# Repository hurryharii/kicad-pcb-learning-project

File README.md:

# Motor Driver Circuit PCB — Work in Progress

## Overview
This project is a motor driver circuit PCB designed using KiCad. It is part of my learning journey in electronics and PCB design.

## Components
- 7805 voltage regulator
- 1N4007 diodes
- Capacitors
- Motor connectors
- Test points

## Current Status
The PCB layout is unfinished, with routing and design checks still pending. It has not yet been fabricated or physically tested.

## Screenshots

### PCB Layout

### 3D PCB View

## Next Steps
- Complete the remaining PCB routing
- Run electrical and design rule checks
- Verify component footprints and connections
- Review the design before fabrication

This project documents my ongoing learning in motor driver circuit design and PCB layout using KiCad.

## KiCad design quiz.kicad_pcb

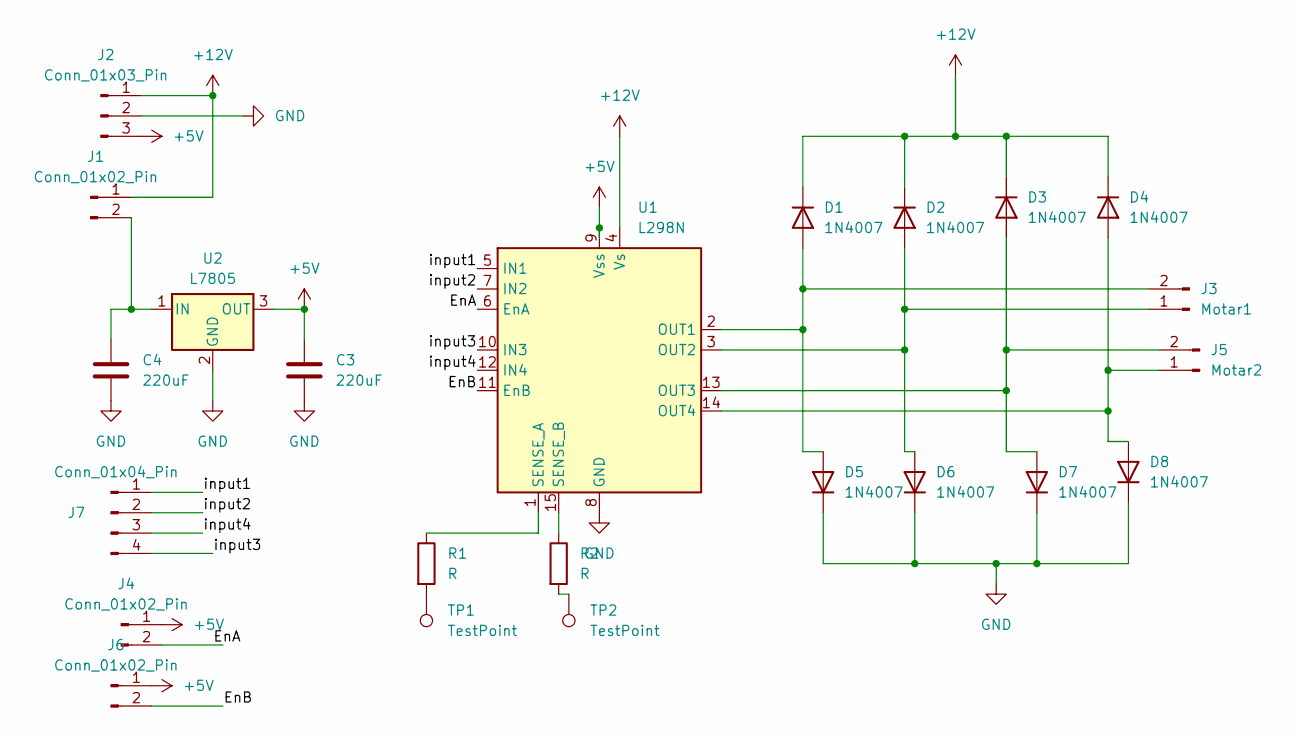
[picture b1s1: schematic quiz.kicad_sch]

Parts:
C3, C4: 220uF; CP_Radial_D10.0mm_P3.50mm
D1, D2, D3, D4, D5, D6, D7, D8: 1N4007; D_DO-41_SOD81_P10.16mm_Horizontal
J1, J4, J6: Conn_01x02_Pin; PinHeader_1x02_P2.54mm_Vertical
J2: Conn_01x03_Pin; TerminalBlock_Phoenix_MPT-0,5-3-2.54_1x03_P2.54mm_Horizontal
J3: Motar1; TerminalBlock_Phoenix_MKDS-1,5-2_1x02_P5.00mm_Horizontal
J5: Motar2; TerminalBlock_Phoenix_MKDS-1,5-2_1x02_P5.00mm_Horizontal
J7: Conn_01x04_Pin; PinHeader_1x04_P2.54mm_Vertical
R1, R2: R; R_0201_0603Metric_Pad0.64x0.40mm_HandSolder
TP1, TP2: TestPoint; TestPoint_Keystone_5010-5014_Multipurpose
U1: L298N; TO-220-15_P2.54x5.08mm_StaggerOdd_Lead4.58mm_Vertical
U2: L7805; TO-220-3_Vertical

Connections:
+5V: C3.1, J2.3, J4.1, J6.1, U1.9 (Vss), U2.3 (OUT)
+12V: D1.1 (K), D2.1 (K), D3.1 (K), D4.1 (K), J1.1, J2.1, U1.4 (Vs)
/EnA: J4.2, U1.6 (EnA)
/EnB: J6.2, U1.11 (EnB)
/input1: J7.1, U1.5 (IN1)
/input2: J7.2, U1.7 (IN2)
/input3: J7.4, U1.10 (IN3)
/input4: J7.3, U1.12 (IN4)
GND: C3.2, C4.2, D5.1 (K), D6.1 (K), D7.1 (K), D8.1 (K), J2.2, U1.8 (GND), U2.2 (GND)
unnamed: D1.2 (A), D5.2 (A), J3.2, U1.2 (OUT1)
unnamed: D2.2 (A), D6.2 (A), J3.1, U1.3 (OUT2)
unnamed: D3.2 (A), D7.2 (A), J5.2, U1.13 (OUT3)
unnamed: D4.2 (A), D8.2 (A), J5.1, U1.14 (OUT4)
unnamed: C4.1, J1.2, U2.1 (IN)
unnamed: R1.2, TP1.1 (1_1)
unnamed: R2.2, TP2.1 (1_1)
unnamed: R1.1, U1.1 (SENSE_A)
unnamed: R2.1, U1.15 (SENSE_B)

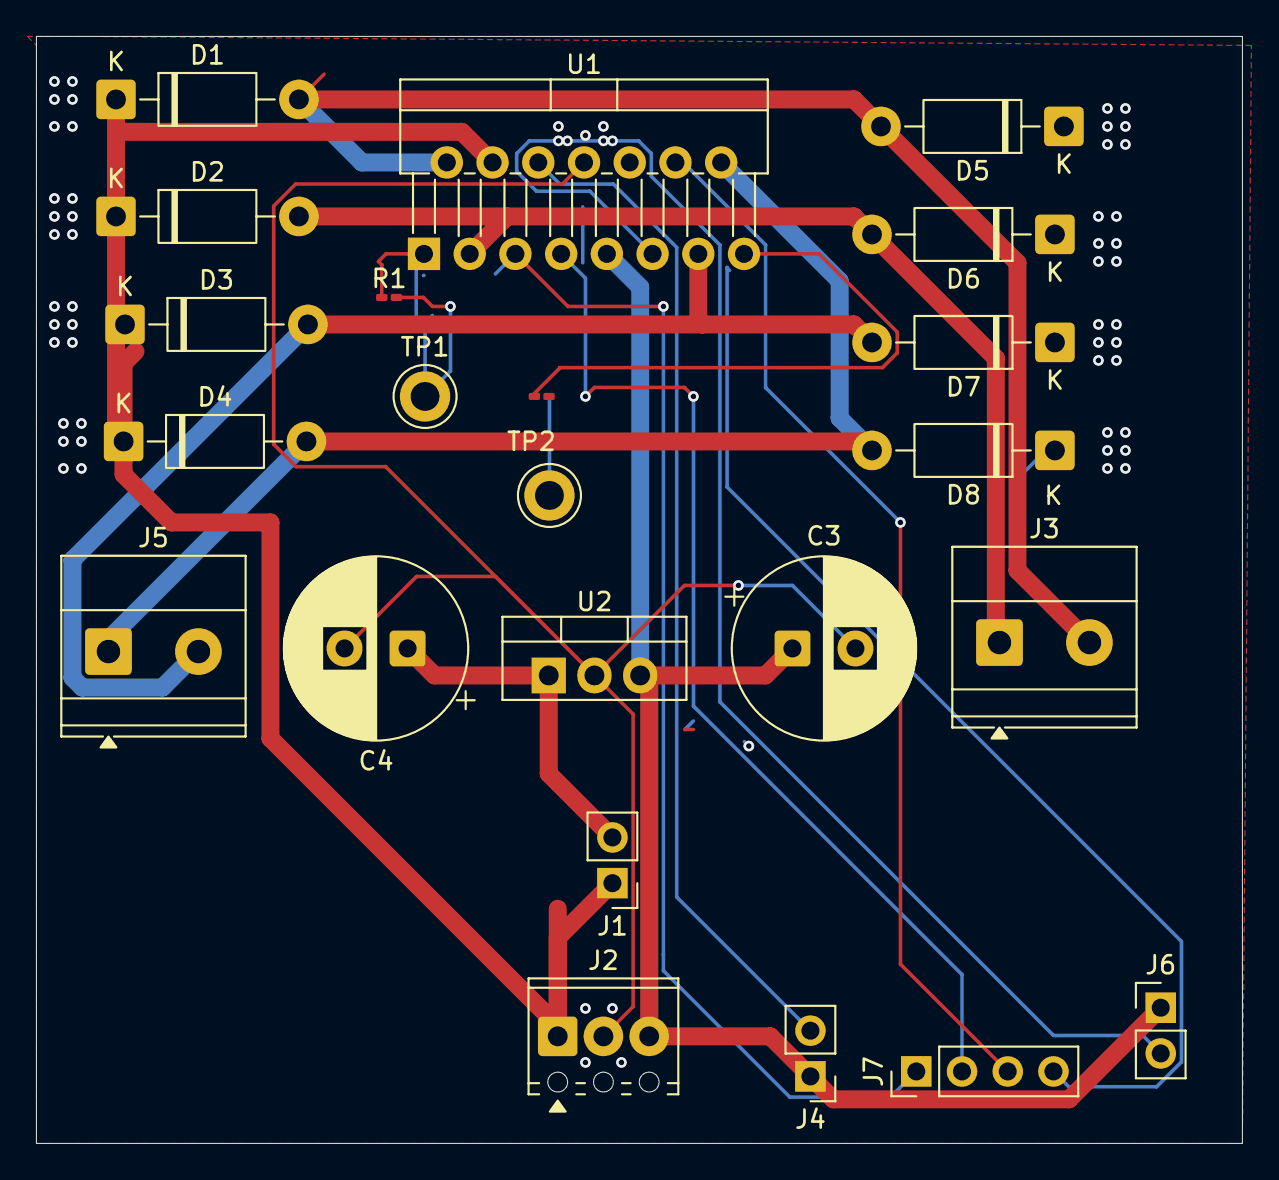
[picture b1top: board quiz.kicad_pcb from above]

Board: 2 copper layers, 67.0 x 61.5 mm, 23 parts (0 on the bottom side), 18 nets.
